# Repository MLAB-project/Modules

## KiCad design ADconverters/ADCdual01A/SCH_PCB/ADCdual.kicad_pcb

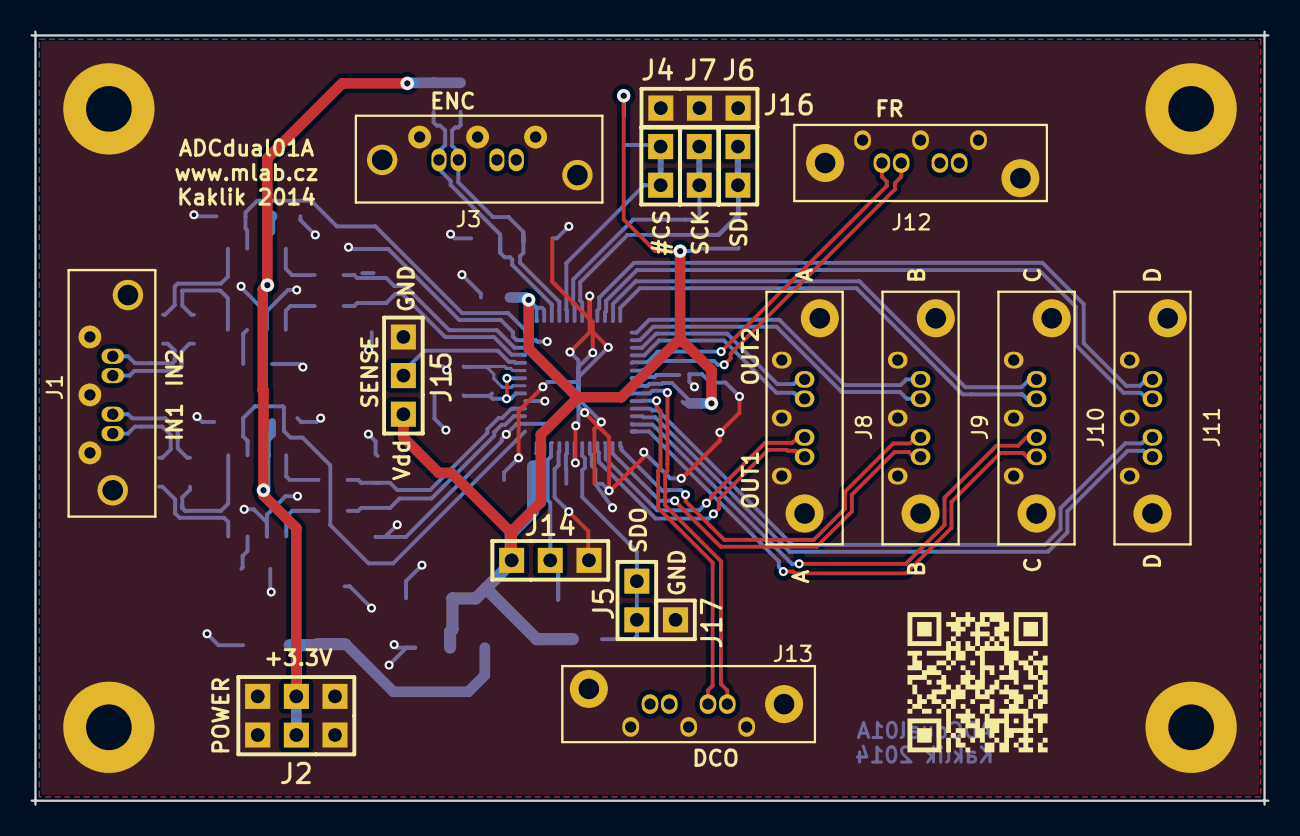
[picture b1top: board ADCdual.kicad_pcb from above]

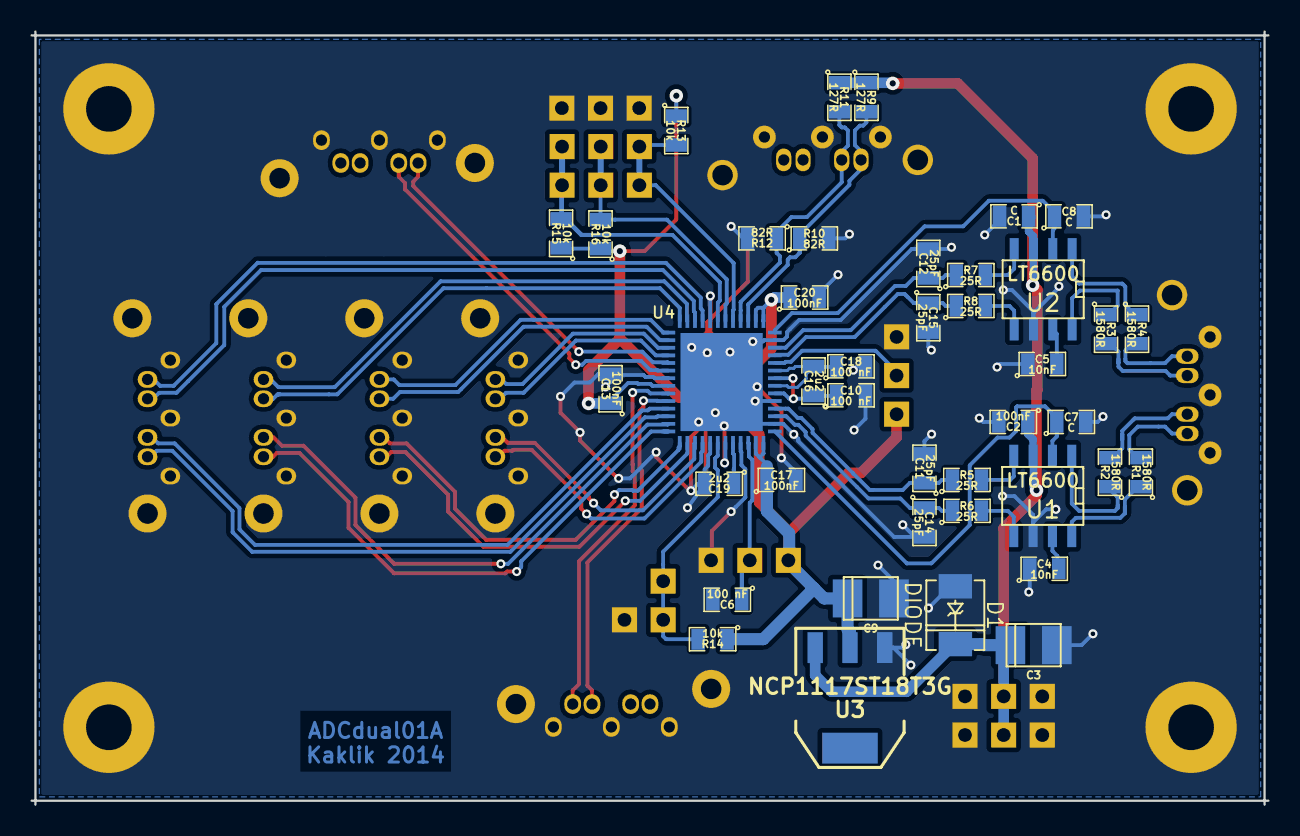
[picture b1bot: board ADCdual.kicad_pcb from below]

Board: 2 copper layers, 81.3 x 50.8 mm, 62 parts (41 on the bottom side), 54 nets.

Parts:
C1, C7, C8: C; SM0805
C2, C13, C17, C20: 100nF; SM0805
C3, C9: 10uF; c_tant_B
C4, C5: 10nF; SM0805
C6, C10, C18: 100 nF; SM0805
C11, C12, C14, C15: 25pF; SM0805
C16, C19: 2u2; SM0805
D1: DIODE; DO-214AC(SMA)
J1, J3: SATA7-67491-1030; SATA-7_THT_VERT
J2: JUMP_3X2_CONN; Pin_Header_Straight_2x03
J4, J5, J6, J7: JUMP_2_CONN; Pin_Header_Straight_2x01
J8, J9, J10, J11, J12, J13: SATA7-67491-1030; SATA-7_THT_VERT_2
J14: SENSE; Pin_Header_Straight_1x03
J15: PAR/SER; Pin_Header_Straight_1x03
J16: CONN_3; Pin_Header_Straight_1x03
J17: CONN_1; Pin_Header_Straight_1x01
P1, P2, P3, P4: CONN_1; MountingHole_3mm
R1, R2, R3, R4: 1580R; SM0805
R5, R6, R7, R8: 25R; SM0805
R9, R11: 127R; SM0805
R10, R12: 82R; SM0805
R13, R14, R15, R16: 10k; SM0805
U1, U2: LT6600; SO8E
U3: NCP1117ST18T3G; SOT223
U4: LTC2271; QFN52+1EP_HandSoldering

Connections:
3V3: C1.1, C2.1, C3.1, D1.2, J2.2, J2.5, R9.1, R11.1, U1.3, U2.3, U3.3
+1.8V: C9.1, C13.1, C17.1, C20.1, J14.1, J15.1, R13.1, R14.1, R15.1, R16.1, U3.2, U4.15, U4.16, U4.34, U4.51, U4.52
DGND: C1.2, C2.2, C3.2, C4.1, C5.1, C6.2, C7.2, C8.2, C9.2, C10.2, C11.2, C12.2, C13.2, C14.2, C15.2, C17.2, C18.2, C19.2, C20.2, D1.1, J1.1, J1.4, J1.7, J1.8, J1.9, J2.1, J2.3, J2.4, J2.6, J3.1, J3.4, J3.7, J3.8, J3.9, J8.1, J8.4, J8.7, J8.8, J8.9, J9.1, J9.4, J9.7, J9.8, J9.9, J10.1, J10.4, J10.7, J10.8, J10.9, J11.1, J11.4, J11.7, J11.8, J11.9, J12.1, J12.4, J12.7, J12.8, J12.9, J13.1, J13.4, J13.7, J13.8, J13.9, J14.3, J15.3, J16.1, J16.2, J16.3, J17.1, P1.1, P2.1, P3.1, P4.1, R10.2, R12.2, U1.6, U2.6, U3.1, U4.2, U4.5, U4.13, U4.22, U4.33, U4.45, U4.47, U4.49, U4.53
unnamed: C4.2, U1.7
unnamed: C5.2, U2.7
unnamed: C6.1, J14.2, U4.50
unnamed: C7.1, U1.2, U4.1
unnamed: C8.1, U2.2, U4.14
unnamed: C10.1, C16.1, U4.6, U4.8
unnamed: C11.1, R5.1, U4.4
unnamed: C12.1, R7.1, U4.12
unnamed: C14.1, R6.1, U4.3
unnamed: C15.1, R8.1, U4.11
unnamed: C16.2, C18.1, U4.7, U4.9
unnamed: C19.1, U4.48
unnamed: J1.2, R1.2
unnamed: J1.3, R2.2
unnamed: J1.5, R3.2
unnamed: J1.6, R4.2
unnamed: J3.2, R9.2, R10.1, U4.17
unnamed: J3.3, R11.2, R12.1, U4.18
unnamed: J4.1, J4.2, R13.2, U4.19
unnamed: J5.1, J5.2, R14.2, U4.46
unnamed: J6.1, J6.2, R15.2, U4.21
unnamed: J7.1, J7.2, R16.2, U4.20
unnamed: J8.2, U4.44
unnamed: J8.3, U4.43
unnamed: J8.5, U4.30
unnamed: J8.6, U4.29
unnamed: J9.2, U4.42
unnamed: J9.3, U4.41
unnamed: J9.5, U4.28
unnamed: J9.6, U4.27
unnamed: J10.2, U4.40
unnamed: J10.3, U4.39
unnamed: J10.5, U4.26
unnamed: J10.6, U4.25
unnamed: J11.2, U4.38
unnamed: J11.3, U4.37
unnamed: J11.5, U4.24
unnamed: J11.6, U4.23
unnamed: J12.2, U4.31
unnamed: J12.3, U4.32
unnamed: J13.2, U4.35
unnamed: J13.3, U4.36
unnamed: J15.2, U4.10
unnamed: R1.1, U1.8
unnamed: R2.1, U1.1
unnamed: R3.1, U2.8
unnamed: R4.1, U2.1
unnamed: R5.2, U1.4
unnamed: R6.2, U1.5
unnamed: R7.2, U2.4
unnamed: R8.2, U2.5

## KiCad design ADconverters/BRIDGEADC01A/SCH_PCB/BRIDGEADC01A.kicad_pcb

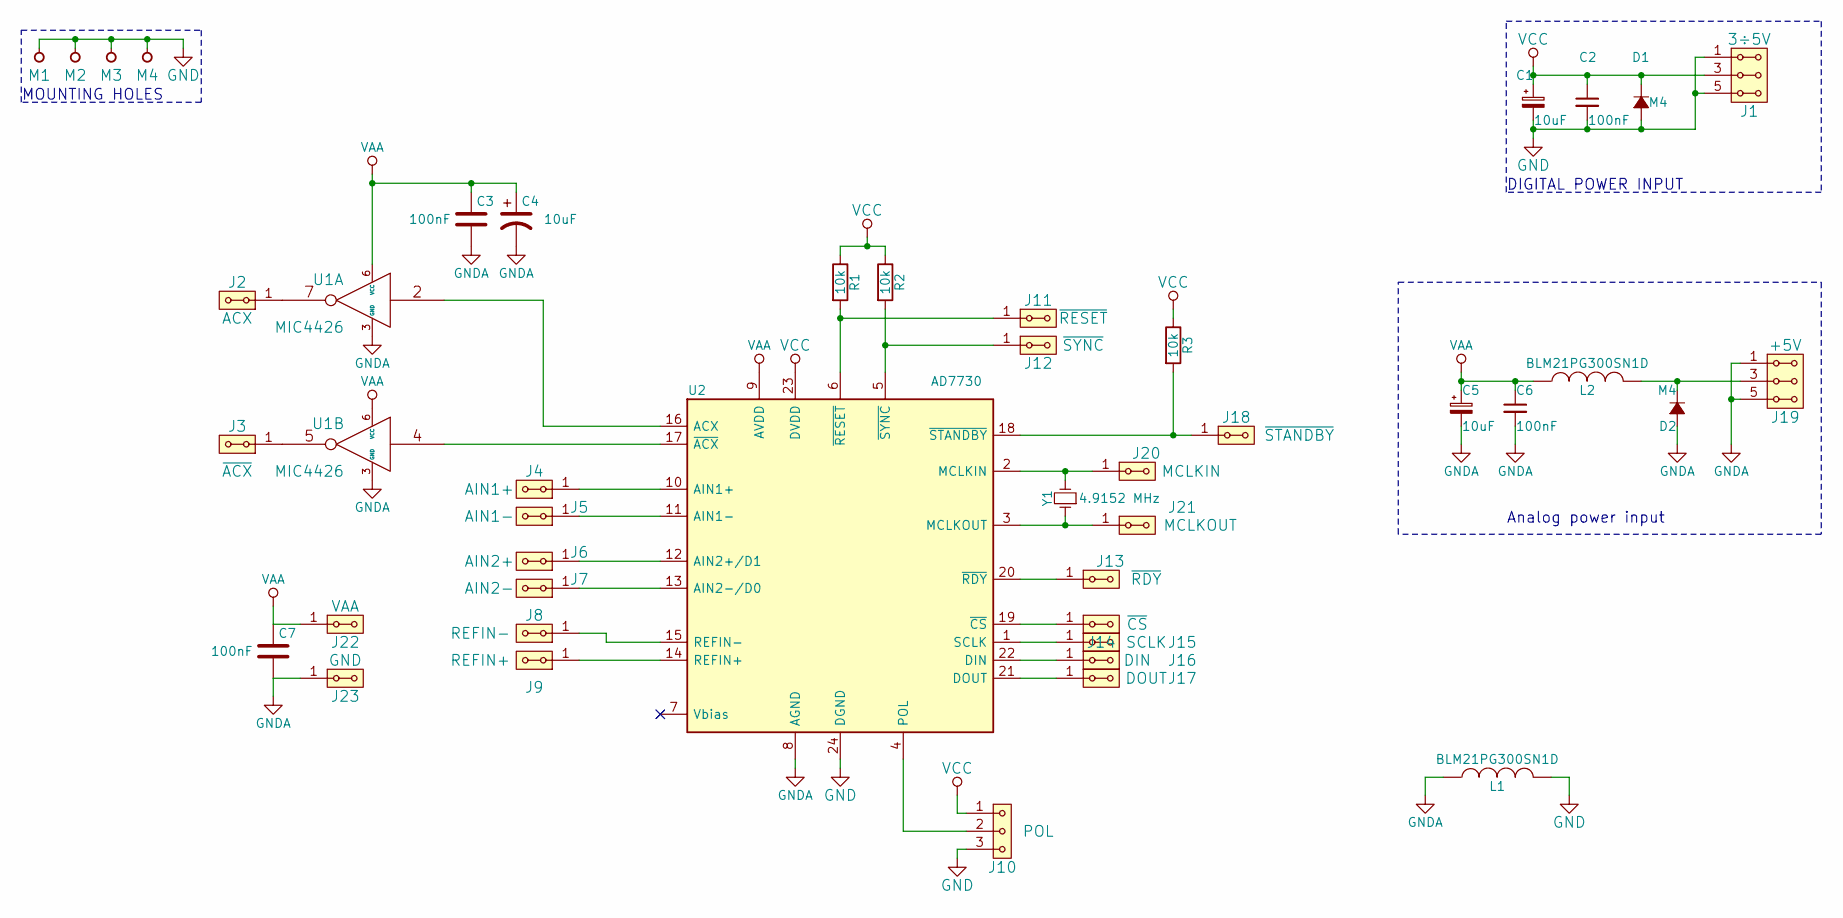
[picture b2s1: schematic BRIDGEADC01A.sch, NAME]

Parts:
C1, C4, C5: 10uF; TantalC_SizeB_EIA-3528_Reflow
C2, C3, C6, C7: 100nF; C_0805
D1, D2: M4; SMA_Standard
J1: 3÷5V; Straight_2x03
J2: ACX; Straight_1x02
J3: ~ACX; Straight_1x02
J4: AIN1+; Straight_1x02
J5: AIN1-; Straight_1x02
J6: AIN2+; Straight_1x02
J7: AIN2-; Straight_1x02
J8: REFIN-; Straight_1x02
J9: REFIN+; Straight_1x02
J10: POL; Straight_1x03
J11: ~RESET; Straight_1x02
J12: ~SYNC; Straight_1x02
J13: ~RDY; Straight_1x02
J14: ~CS; Straight_1x02
J15: SCLK; Straight_1x02
J16: DIN; Straight_1x02
J17: DOUT; Straight_1x02
J18: ~STANDBY; Straight_1x02
J19: +5V; Straight_2x03
J20: MCLKIN; Straight_1x02
J21: MCLKOUT; Straight_1x02
J22: VAA; Straight_1x02
J23: GND; Straight_1x02
L1, L2: BLM21PG300SN1D; C_0805
M1, M2, M3, M4: HOLE; MountingHole_3mm
R1, R2, R3: 10k; R_0805
U1: MIC4426; SOIC-8_3.9x4.9mm_Pitch1.27mm
U2: AD7730; TSSOP-24_4.4x7.8mm_Pitch0.65mm
Y1: 4.9152 MHz; Crystal_HC49-U_Vertical

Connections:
GND: C1.2, C2.2, D1.2 (A), J1.1, J1.2, J1.5, J1.6, J10.3, L1.2, M1.1, M2.1, M3.1, M4.1, U2.24 (DGND)
GNDA: C3.2, C4.2, C5.2, C6.2, C7.2, D2.2 (A), J19.1, J19.2, J19.5, J19.6, J23.1, J23.2, L1.1, U1.3 (GND), U2.8 (AGND)
unnamed: D2.1 (K), J19.3, J19.4, L2.2
unnamed: J2.1, J2.2, U1.7
unnamed: J3.1, J3.2, U1.5
unnamed: J4.1, J4.2, U2.10 (AIN1+)
unnamed: J5.1, J5.2, U2.11 (AIN1-)
unnamed: J6.1, J6.2, U2.12 (AIN2+/D1)
unnamed: J7.1, J7.2, U2.13 (AIN2-/D0)
unnamed: J8.1, J8.2, U2.15 (REFIN-)
unnamed: J9.1, J9.2, U2.14 (REFIN+)
unnamed: J10.2, U2.4 (POL)
unnamed: J11.1, J11.2, R1.2, U2.6 (~RESET)
unnamed: J12.1, J12.2, R2.2, U2.5 (~SYNC)
unnamed: J13.1, J13.2, U2.20 (~RDY)
unnamed: J14.1, J14.2, U2.19 (~CS)
unnamed: J15.1, J15.2, U2.1 (SCLK)
unnamed: J16.1, J16.2, U2.22 (DIN)
unnamed: J17.1, J17.2, U2.21 (DOUT)
unnamed: J18.1, J18.2, R3.2, U2.18 (~STANDBY)
unnamed: J20.1, J20.2, U2.2 (MCLKIN), Y1.2
unnamed: J21.1, J21.2, U2.3 (MCLKOUT), Y1.1
unnamed: U1.2, U2.16 (ACX)
unnamed: U1.4, U2.17 (~ACX)
VAA: C3.1, C4.1, C5.1, C6.1, C7.1, J22.1, J22.2, L2.1, U1.6 (VCC), U2.9 (AVDD)
VCC: C1.1, C2.1, D1.1 (K), J1.3, J1.4, J10.1, R1.1, R2.1, R3.1, U2.23 (DVDD)

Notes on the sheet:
DIGITAL POWER INPUT
MOUNTING HOLES
Analog power input

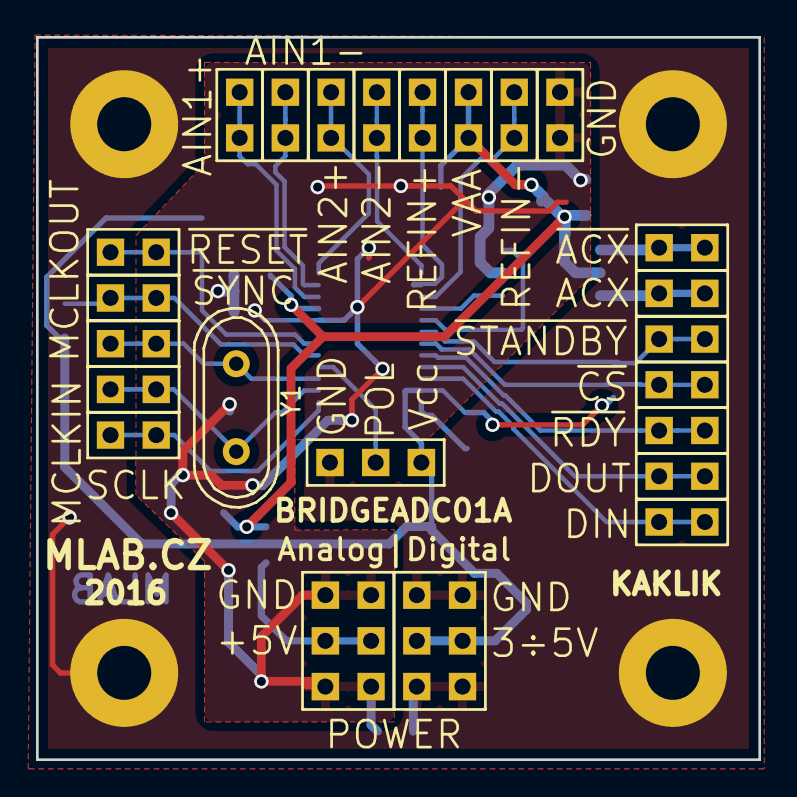
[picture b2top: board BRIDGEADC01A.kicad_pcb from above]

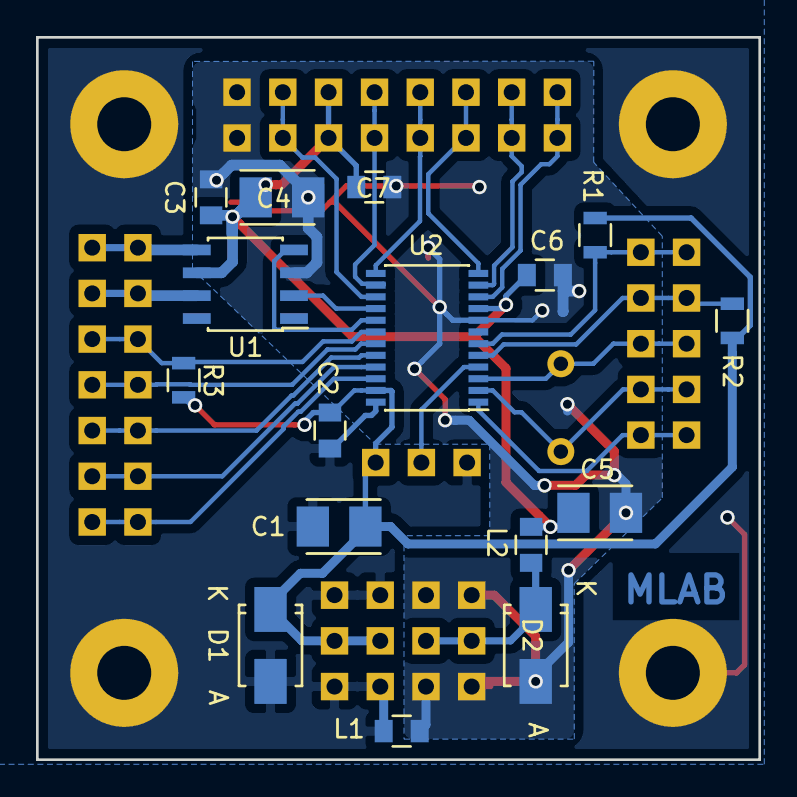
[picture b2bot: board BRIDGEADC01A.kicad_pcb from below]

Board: 2 copper layers, 40.1 x 40.1 mm, 44 parts (16 on the bottom side), 26 nets.

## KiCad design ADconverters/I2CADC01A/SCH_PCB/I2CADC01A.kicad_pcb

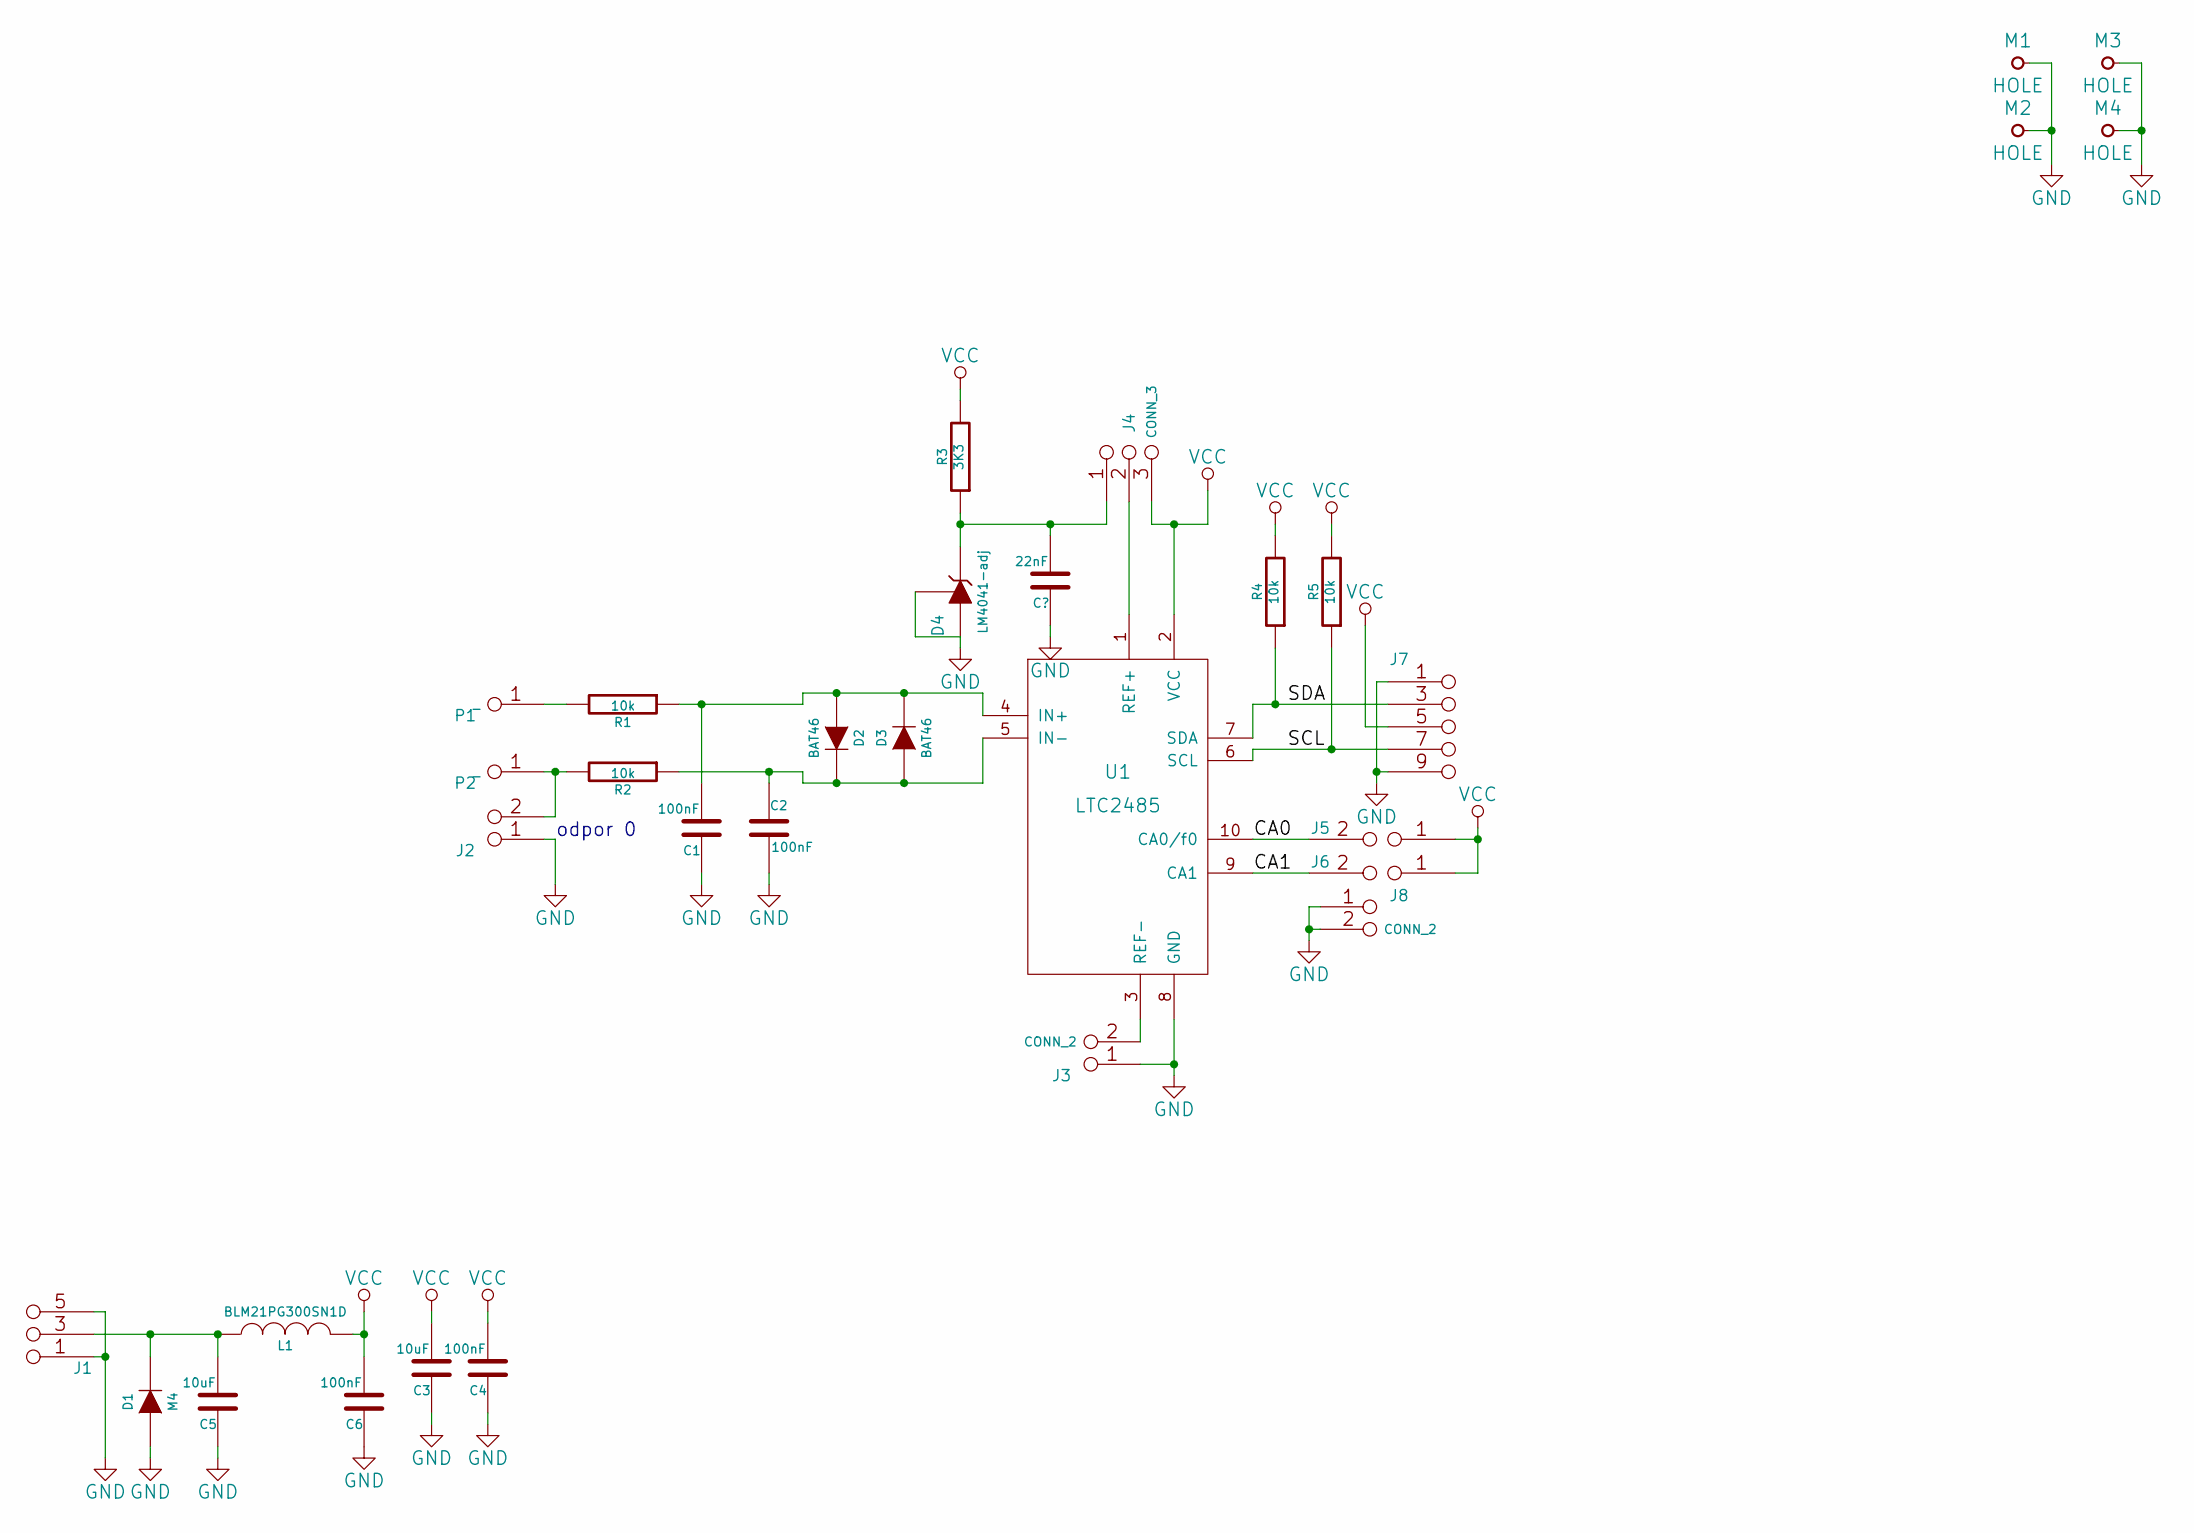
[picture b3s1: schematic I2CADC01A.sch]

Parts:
C1, C2, C4, C6: 100nF; SMD-0805
C3, C5: 10uF; SMD-0805
D1: M4; SMA_Standard
D2, D3: BAT46; MiniMELF_Standard
D4: LM4041-adj; SOT-23
J1: JUMP_3X2; Straight_2x03
J2: CONN1_2; Straight_2x01
J3, J8: CONN_2; Straight_2x01
J4: CONN_3; Straight_1x03
J5, J6: JUMP2_2x1; Straight_2x01
J7: JUMP_5X2; Straight_2x05
L1: BLM21PG300SN1D; SMD-0805
M1, M2, M3, M4: HOLE; MountingHole_3mm
P1, P2: _; WAGO256
R1, R2, R4, R5: 10k; SMD-0805
R3: 3K3; SMD-0805
U1: LTC2485; DFN-10-1EP_3x3mm_Pitch0.5mm

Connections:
/CA0: J5.2, U1.10 (CA0/f0)
/CA1: J6.2, U1.9 (CA1)
/SCL: J7.7, J7.8 (7), R5.1, U1.6 (SCL)
/SDA: J7.3 (4), J7.4, R4.1, U1.7 (SDA)
GND: C1.1, C2.2, C3.1, C4.1, C5.1, C6.1, D1.1 (A), D4.2, D4.3 (A), J1.1 (2), J1.2, J1.5 (6), J1.6, J2.1, J3.1, J7.1 (2), J7.2, J7.9 (10), J7.10, J8.1, J8.2 (PM), M1.1, M2.1, M3.1, M4.1, U1.8 (GND), U1.11 (GND); also elsewhere on the board
unnamed: C1.2, D2.1 (A), D3.2 (K), R1.1, U1.4 (IN+)
unnamed: C2.1, D2.2 (K), D3.1 (A), R2.1, U1.5 (IN-)
unnamed 7: C5.2, D1.2 (K), J1.3 (4), J1.4, L1.1; also elsewhere on the board
unnamed 8: D4.1 (K), J4.1, R3.1; also elsewhere on the board
unnamed: J3.2 (PM), U1.3 (REF-)
unnamed: J4.2 (PM), U1.1 (REF+)
unnamed: P1.1, R1.2
unnamed 12: J2.2 (PM), P2.1, R2.2; also elsewhere on the board
VCC: C3.2, C4.2, C6.2, J4.3, J5.1, J6.1, J7.5 (6), J7.6, L1.2, R3.2, R4.2, R5.2, U1.2 (VCC)

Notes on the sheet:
odpor 0

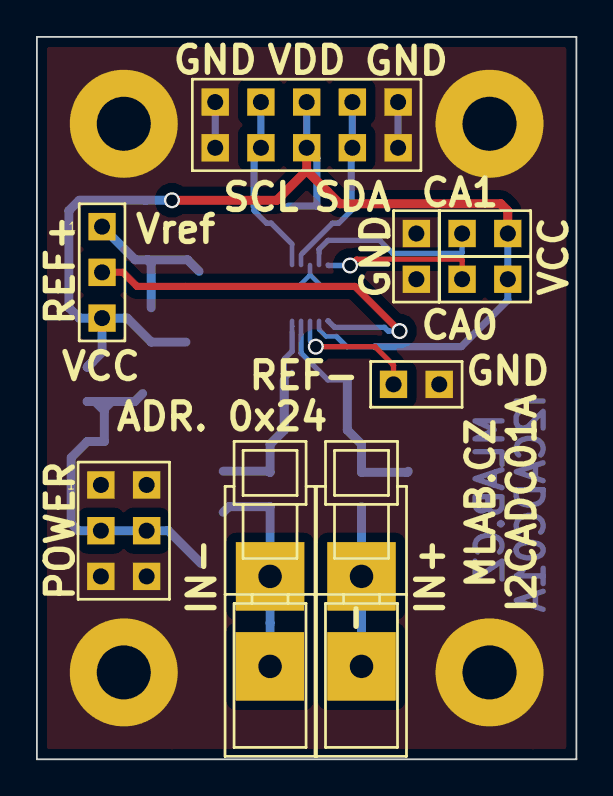
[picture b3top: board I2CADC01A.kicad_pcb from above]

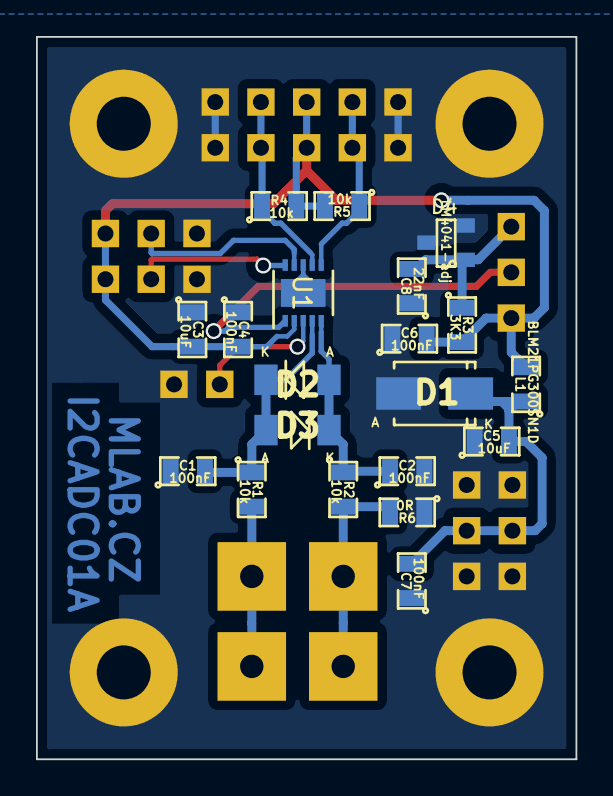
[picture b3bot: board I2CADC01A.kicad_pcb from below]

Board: 2 copper layers, 30.0 x 40.1 mm, 33 parts (20 on the bottom side), 14 nets.

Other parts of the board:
C7: 100nF; SMD-0805
C8: 22nF; SMD-0805
R6: 0R; SMD-0805

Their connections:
GND: C7.1, C8.1, R6.1; also elsewhere on the board
unnamed 7: C7.2; also elsewhere on the board
unnamed 8: C8.2; also elsewhere on the board
unnamed 12: R6.2; also elsewhere on the board

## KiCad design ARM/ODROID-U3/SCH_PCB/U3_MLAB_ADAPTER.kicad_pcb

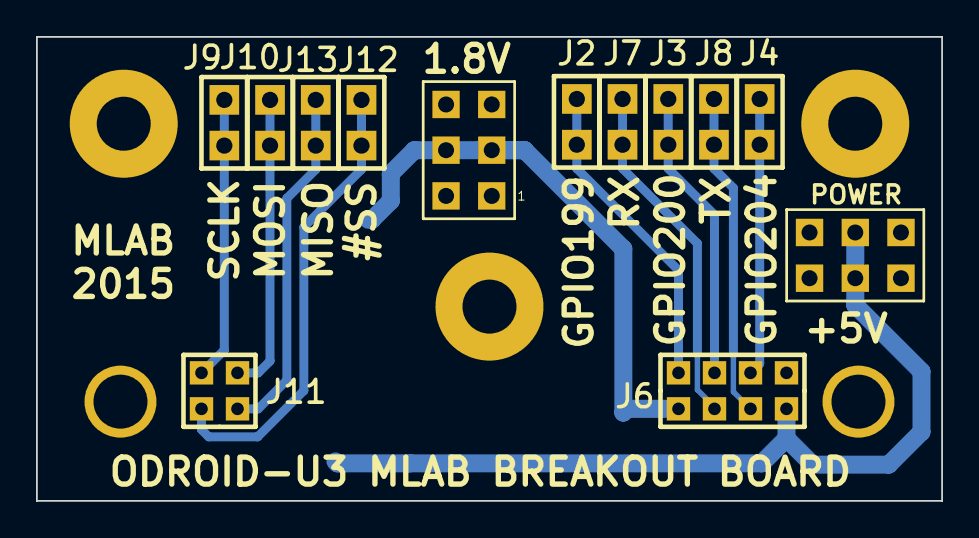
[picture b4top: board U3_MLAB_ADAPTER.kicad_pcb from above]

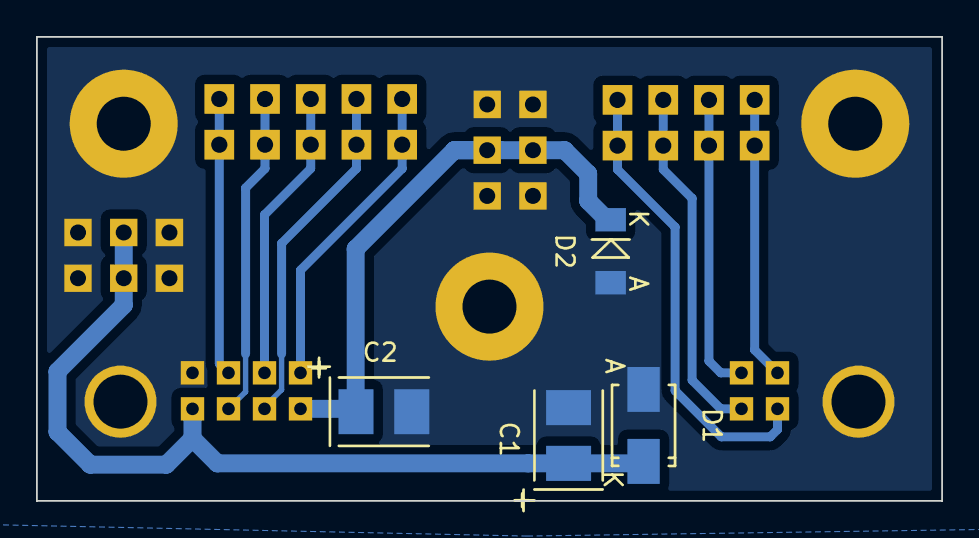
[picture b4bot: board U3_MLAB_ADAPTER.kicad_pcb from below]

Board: 2 copper layers, 50.3 x 25.8 mm, 22 parts (4 on the bottom side), 12 nets.

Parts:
C1, C2: 10uF; TantalC_SizeB_EIA-3528_Reflow
D1: BAS85; Diode-SMA_Standard
D2: BAS85; Diode-MiniMELF_Standard
J1: 5V POWER; Straight_2x03
J2: GPIO199; Pin_Header_Straight_2x01
J3: GPIO200; Pin_Header_Straight_2x01
J4: GPIO204; Pin_Header_Straight_2x01
J5: 1,8V CPU Core; Straight_2x03
J6: IOS_PORT_#1; 2mm_Pin_Header_Straight_2x04
J7: UART_RX; Pin_Header_Straight_2x01
J8: UART_TX; Pin_Header_Straight_2x01
J9: SCLK; Pin_Header_Straight_2x01
J10: MOSI; Pin_Header_Straight_2x01
J11: IO_PORT_#2; 2mm_Pin_Header_Straight_2x02
J12: #SS; Pin_Header_Straight_2x01
J13: MISO; Pin_Header_Straight_2x01
J14, J15, J16, J17, J18: M3; MountingHole_3mm

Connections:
+1.8V: C2.1, D2.2, J5.3, J5.4, J6.1
+5V: C1.1, D1.2, J1.3, J1.4, J6.7
/GPIO199: J2.1, J2.2, J6.2
/GPIO200: J3.1, J3.2, J6.4
/GPIO204: J4.1, J4.2, J6.6
/MISO: J11.4, J13.1, J13.2
/SCLK: J9.1, J9.2, J11.1
/UART_RX: J6.3, J7.1, J7.2
/UART_TX: J6.5, J8.1, J8.2
GND: C1.2, C2.2, D1.1, D2.1, J1.1, J1.2, J1.5, J1.6, J5.1, J5.2, J5.5, J5.6, J6.8, J14.1, J15.1, J16.1, J17.1, J18.1
unnamed: J10.1, J10.2, J11.2
unnamed: J11.3, J12.1, J12.2

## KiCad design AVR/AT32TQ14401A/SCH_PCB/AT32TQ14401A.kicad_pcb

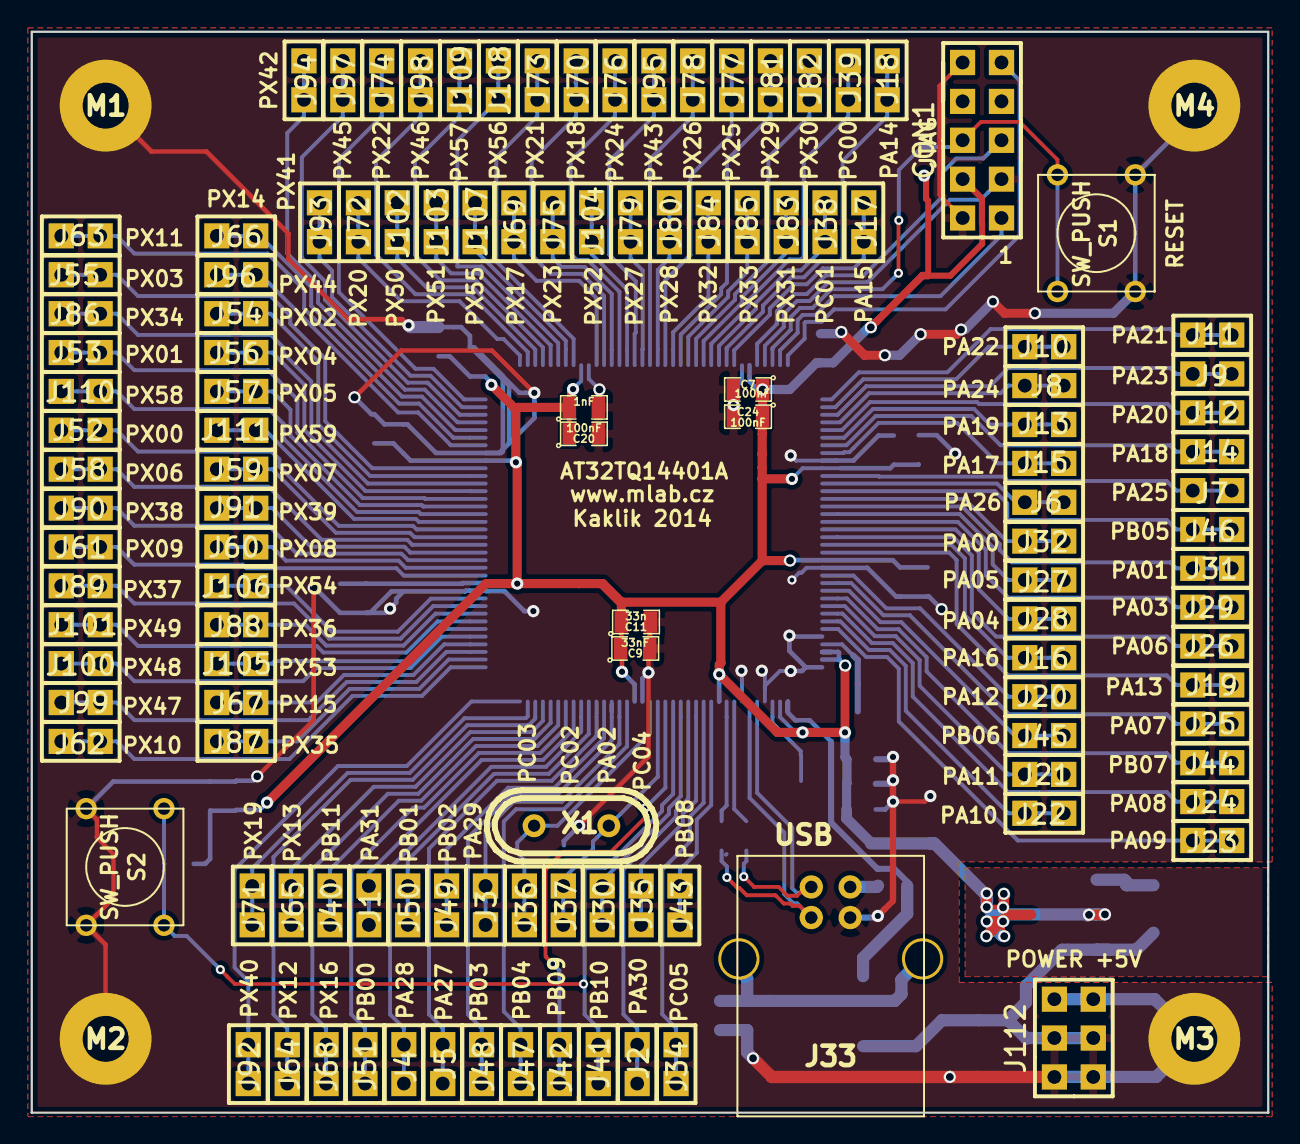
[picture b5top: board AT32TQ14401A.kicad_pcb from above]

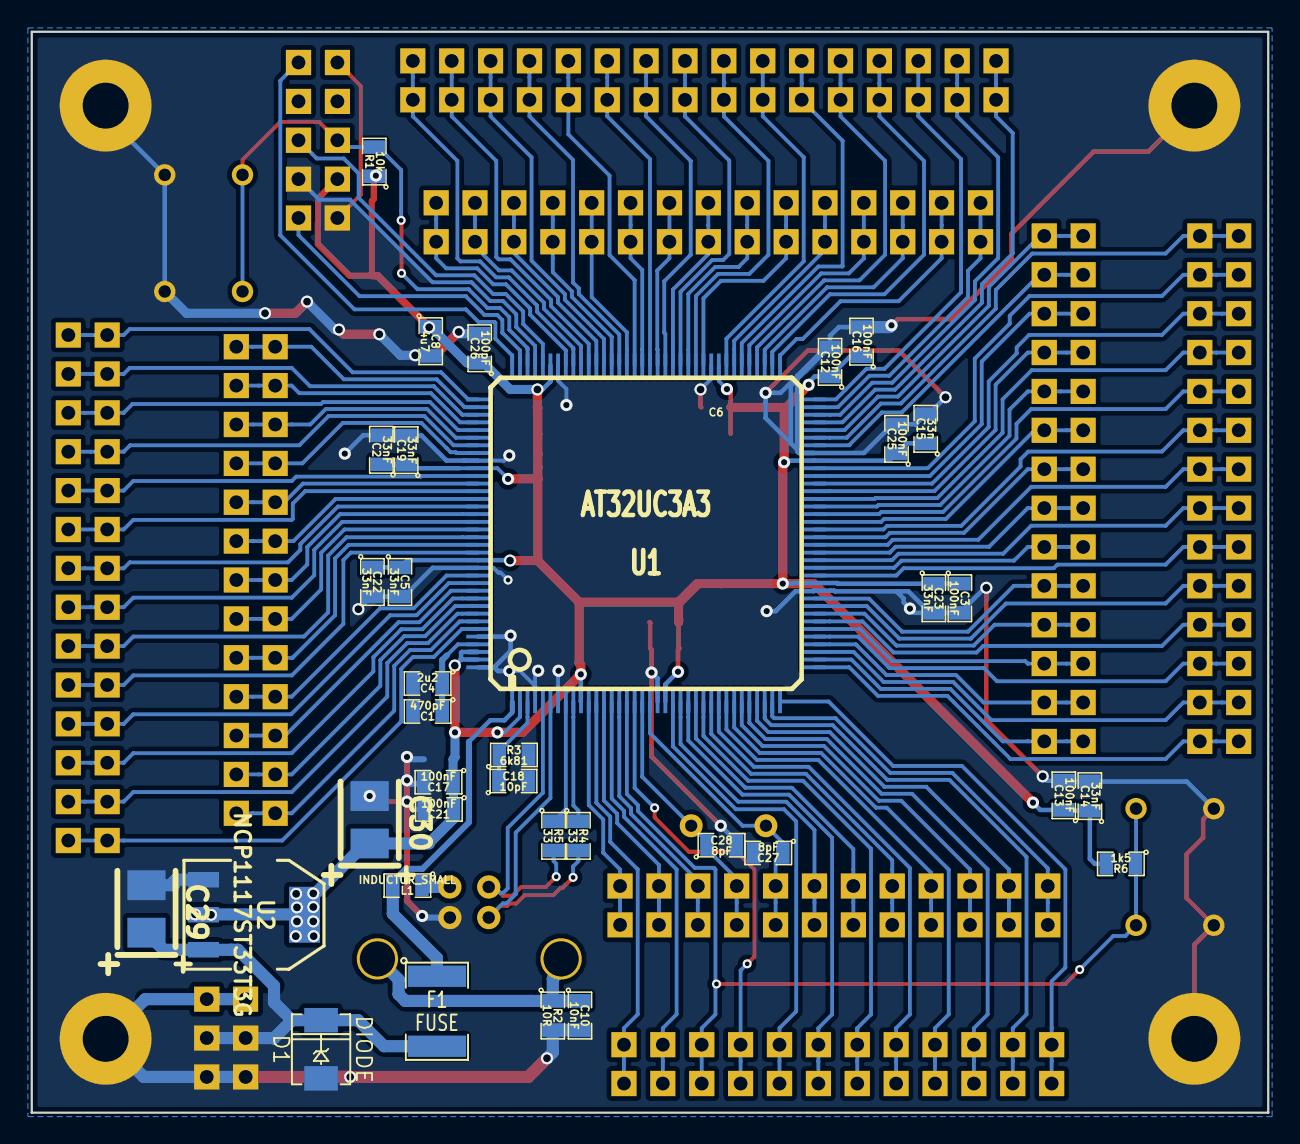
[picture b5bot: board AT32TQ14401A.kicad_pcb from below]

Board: 2 copper layers, 80.8 x 70.6 mm, 161 parts (35 on the bottom side), 127 nets.

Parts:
C1: 470pF; SM0805
C2, C5, C9, C14, C19, C22, C23: 33nF; SM0805
C3, C7, C12, C13, C16, C17, C20, C21, C24, C25: 100nF; SM0805
C4: 2u2; SM0805
C6: 1nF; SM0805
C8: 4u7; SM0805
C10: 10nF; SM0805
C11, C15: 33n; SM0805
C18: 10pF; SM0805
C26: 100pF; SM0805
C27, C28: 8pF; SM0805
C29, C30: 10uF; TantalC_SizeB_EIA-3528_Reflow
CON1: AVR-JTAG-10; Pin_Header_Straight_2x05
D1: DIODE; DO-214AC(SMA)
F1: FUSE; SM1812
J1, J2, J3, J4, J5, J6, J7, J8, J9, J10, J11, J12, J13, J14, J15, J16, J17, J18, J19, J20, J21, J22, J23, J24, J25, J26, J27, J28, J29, J30, J31, J32, J34, J35, J36, J37, J38, J39, J40, J41, J42, J43, J44, J45, J46, J47, J48, J49, J50, J51, J52, J53, J54, J55, J56, J57, J58, J59, J60, J61, J62, J63, J64, J65, J66, J67, J68, J69, J70, J71, J72, J73, J74, J75, J76, J77, J78, J79, J80, J81, J82, J83, J84, J85, J86, J87, J88, J89, J90, J91, J92, J93, J94, J95, J96, J97, J98, J99, J100, J101, J102, J103, J104, J105, J106, J107, J108, J109, J110, J111: JUMP_2_CONN; Pin_Header_Straight_2x01
J33: USB; USB_B
J112: HEADER_2x03_PARALLEL; Pin_Header_Straight_2x03
L1: INDUCTOR_SMALL; SM0805
M1, M2, M3, M4: HOLE 3mm; MountingHole_3mm
R1: 10k; SM0805
R2: 10R; SM0805
R3: 6k81; SM0805
R4, R5: 33; SM0805
R6: 1k5; SM0805
S1, S2: SW_PUSH; SW_PUSH_SMALL
U1: AT32UC3A3; TQFP144
U2: NCP1117ST33T3G; SOT223
X1: 12MHz; Crystal_HC49-U_Vertical

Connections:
3V3: C2.1, C3.1, C5.1, C6.1, C7.1, C8.1, C9.1, C11.1, C12.1, C13.1, C14.1, C15.1, C16.1, C17.1, C19.1, C20.1, C21.1, C22.1, C23.1, C24.1, C25.1, C26.1, C30.1, CON1.4, R1.1, R6.2, U1.2, U1.10, U1.21, U1.48, U1.64, U1.81, U1.103, U1.118, U1.130, U1.142, U1.143, U2.2
+5V: C29.1, D1.2, F1.2, J112.3, J112.4, U2.3
GND: C1.2, C2.2, C3.2, C4.2, C5.2, C6.2, C7.2, C8.2, C9.2, C10.2, C11.2, C12.2, C13.2, C14.2, C15.2, C16.2, C17.2, C18.2, C19.2, C20.2, C21.2, C22.2, C23.2, C24.2, C25.2, C26.2, C27.2, C28.2, C29.2, C30.2, CON1.2, CON1.10, D1.1, J33.4, J112.1, J112.2, J112.5, J112.6, M1.1, M2.1, M3.1, M4.1, R2.2, R3.2, S1.1, S2.2, U1.4, U1.7, U1.20, U1.47, U1.65, U1.82, U1.102, U1.117, U1.131, U1.140, U1.144, U2.1
unnamed: C1.1, C4.1, U1.141
unnamed: C10.1, J33.5, J33.6, R2.1
unnamed: C18.1, R3.1, U1.3
unnamed: C27.1, J36.1, J36.2, U1.19, X1.1
unnamed: C28.1, J37.1, J37.2, U1.18, X1.2
unnamed: CON1.1, U1.107
unnamed: CON1.3, U1.105
unnamed: CON1.5, U1.104
unnamed: CON1.6, R1.2, S1.2, U1.106
unnamed: CON1.9, U1.108
unnamed: F1.1, L1.2, U1.1
unnamed: J1.1, J1.2, U1.29
unnamed: J2.1, J2.2, U1.14
unnamed: J3.1, J3.2, U1.23
unnamed: J4.1, J4.2, U1.28
unnamed: J5.1, J5.2, U1.26
unnamed: J6.1, J6.2, U1.120
unnamed: J7.1, J7.2, U1.119
unnamed: J8.1, J8.2, U1.112
unnamed: J9.1, J9.2, U1.111
unnamed: J10.1, J10.2, U1.110
unnamed: J11.1, J11.2, U1.109
unnamed: J12.1, J12.2, U1.113
unnamed: J13.1, J13.2, U1.114
unnamed: J14.1, J14.2, U1.115
unnamed: J15.1, J15.2, U1.116
unnamed: J16.1, J16.2, U1.128
unnamed: J17.1, J17.2, U1.101
unnamed: J18.1, J18.2, U1.100
unnamed: J19.1, J19.2, U1.129
unnamed: J20.1, J20.2, U1.132
unnamed: J21.1, J21.2, U1.136
unnamed: J22.1, J22.2, U1.138
unnamed: J23.1, J23.2, U1.139
unnamed: J24.1, J24.2, U1.137
unnamed: J25.1, J25.2, U1.133
unnamed: J26.1, J26.2, U1.127
unnamed: J27.1, J27.2, U1.124
unnamed: J28.1, J28.2, U1.126
unnamed: J29.1, J29.2, U1.125
unnamed: J30.1, J30.2, U1.15
unnamed: J31.1, J31.2, U1.123
unnamed: J32.1, J32.2, U1.122
unnamed: J33.1, L1.1
unnamed: J33.2, R5.2, U1.5
unnamed: J33.3, R4.2, U1.6
unnamed: J34.1, J34.2, U1.12
unnamed: J35.1, J35.2, U1.13
unnamed: J38.1, J38.2, U1.99
unnamed: J39.1, J39.2, U1.98
unnamed: J40.1, J40.2, U1.31
unnamed: J41.1, J41.2, R6.1, S2.1, U1.16
unnamed: J42.1, J42.2, U1.17
unnamed: J43.1, J43.2, U1.11
unnamed: J44.1, J44.2, U1.135
unnamed: J45.1, J45.2, U1.134
unnamed: J46.1, J46.2, U1.121
unnamed: J47.1, J47.2, U1.22
unnamed: J48.1, J48.2, U1.24
unnamed: J49.1, J49.2, U1.25
unnamed: J50.1, J50.2, U1.27
unnamed: J51.1, J51.2, U1.30
unnamed: J52.1, J52.2, U1.55
unnamed: J53.1, J53.2, U1.59
unnamed: J54.1, J54.2, U1.62
unnamed: J55.1, J55.2, U1.63
unnamed: J56.1, J56.2, U1.60
unnamed: J57.1, J57.2, U1.58
unnamed: J58.1, J58.2, U1.53
unnamed: J59.1, J59.2, U1.54
unnamed: J60.1, J60.2, U1.50
unnamed: J61.1, J61.2, U1.49
unnamed: J62.1, J62.2, U1.37
unnamed: J63.1, J63.2, U1.67
unnamed: J64.1, J64.2, U1.34
unnamed: J65.1, J65.2, U1.33
unnamed: J66.1, J66.2, U1.68
unnamed: J67.1, J67.2, U1.40
unnamed: J68.1, J68.2, U1.32
unnamed: J69.1, J69.2, U1.83
unnamed: J70.1, J70.2, U1.84
unnamed: J71.1, J71.2, U1.35
unnamed: J72.1, J72.2, U1.73
unnamed: J73.1, J73.2, U1.80
unnamed: J74.1, J74.2, U1.72
unnamed: J75.1, J75.2, U1.85
unnamed: J76.1, J76.2, U1.86
unnamed: J77.1, J77.2, U1.92
unnamed: J78.1, J78.2, U1.90
unnamed: J79.1, J79.2, U1.89
unnamed: J80.1, J80.2, U1.91
unnamed: J81.1, J81.2, U1.94
unnamed: J82.1, J82.2, U1.96
unnamed: J83.1, J83.2, U1.97
unnamed: J84.1, J84.2, U1.93
unnamed: J85.1, J85.2, U1.95
unnamed: J86.1, J86.2, U1.61
unnamed: J87.1, J87.2, U1.38
unnamed: J88.1, J88.2, U1.44
unnamed: J89.1, J89.2, U1.45
unnamed: J90.1, J90.2, U1.51
unnamed: J91.1, J91.2, U1.52
unnamed: J92.1, J92.2, U1.36
unnamed: J93.1, J93.2, U1.71
unnamed: J94.1, J94.2, U1.69
unnamed: J95.1, J95.2, U1.88
unnamed: J96.1, J96.2, U1.66
unnamed: J97.1, J97.2, U1.70
unnamed: J98.1, J98.2, U1.74
unnamed: J99.1, J99.2, U1.39
unnamed: J100.1, J100.2, U1.41
unnamed: J101.1, J101.2, U1.43
unnamed: J102.1, J102.2, U1.75
unnamed: J103.1, J103.2, U1.77
unnamed: J104.1, J104.2, U1.87
unnamed: J105.1, J105.2, U1.42
unnamed: J106.1, J106.2, U1.46
unnamed: J107.1, J107.2, U1.79
unnamed: J108.1, J108.2, U1.78
unnamed: J109.1, J109.2, U1.76
unnamed: J110.1, J110.2, U1.57
unnamed: J111.1, J111.2, U1.56
unnamed: R4.1, U1.9
unnamed: R5.1, U1.8
